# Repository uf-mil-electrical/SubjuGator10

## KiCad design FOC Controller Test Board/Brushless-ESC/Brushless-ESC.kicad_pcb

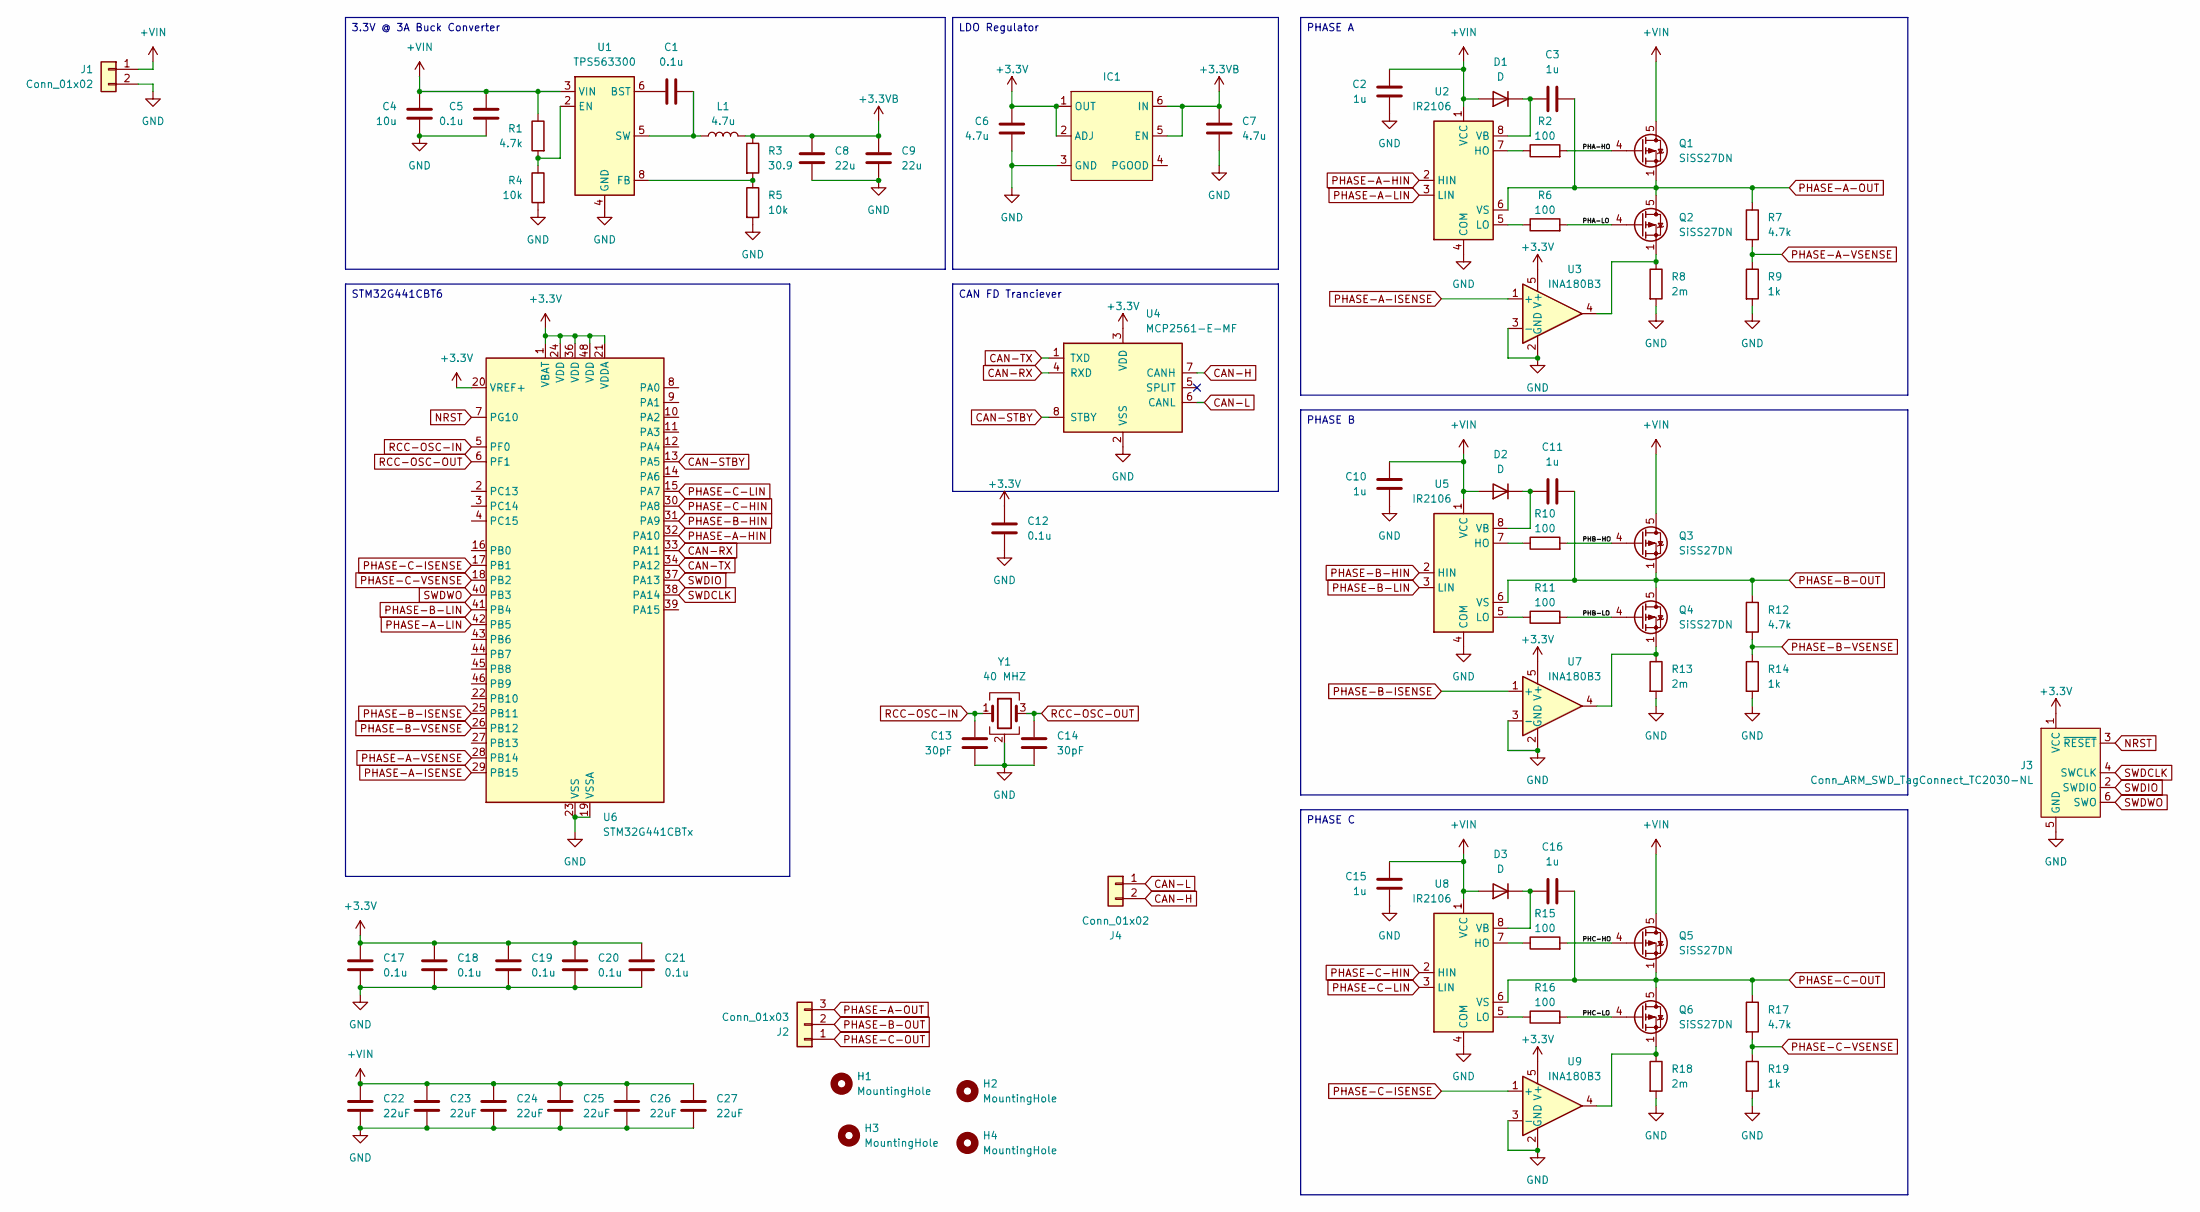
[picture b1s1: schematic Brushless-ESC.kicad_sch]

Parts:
C1, C5, C12, C17, C18, C19, C20, C21: 0.1u; C_0402_1005Metric
C2, C3, C10, C11, C15, C16: 1u; C_0603_1608Metric
C4: 10u; C_0805_2012Metric
C6, C7: 4.7u; C_0603_1608Metric
C8, C9: 22u; C_0805_2012Metric
C13, C14: 30pF; C_0402_1005Metric
C22, C23, C24, C25, C26, C27: 22uF; C_0805_2012Metric
D1, D2, D3: D; D_SOD-323
H1, H2, H3, H4: MountingHole; MountingHole_3.2mm_M3_Pad_Via
IC1: SON95P300X300X100-7N-D
J1: Conn_01x02; Wago_734-162_1x02_P3.50mm_Horizontal
J2: Conn_01x03; Wago_734-163_1x03_P3.50mm_Horizontal
J3: Conn_ARM_SWD_TagConnect_TC2030-NL; Tag-Connect_TC2030-IDC-NL_2x03_P1.27mm_Vertical
J4: Conn_01x02; TerminalBlock_Xinya_XY308-2.54-2P_1x02_P2.54mm_Horizontal
L1: 4.7u; L_Coilcraft_LPS3314
Q1, Q2, Q3, Q4, Q5, Q6: SiSS27DN; Vishay_PowerPAK_1212-8_Single
R1, R7, R12, R17: 4.7k; R_0402_1005Metric
R2, R6, R10, R11, R15, R16: 100; R_0402_1005Metric
R3: 30.9; R_0402_1005Metric
R4, R5: 10k; R_0402_1005Metric
R8, R13, R18: 2m; R_1206_3216Metric
R9, R14, R19: 1k; R_0402_1005Metric
U1: TPS563300; SOT-583-8
U2, U5, U8: IR2106; SOIC-8_3.9x4.9mm_P1.27mm
U3, U7, U9: INA180B3; SOT-23-5
U4: MCP2561-E-MF; DFN-8-1EP_3x3mm_P0.65mm_EP1.55x2.4mm
U6: STM32G441CBTx; LQFP-48_7x7mm_P0.5mm
Y1: 40 MHZ; Crystal_SMD_3225-4Pin_3.2x2.5mm

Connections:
+3.3V: C6.1, C12.1, C17.1, C18.1, C19.1, C20.1, C21.1, IC1.1 (OUT), IC1.2 (ADJ), J3.1 (VCC), U3.5 (V+), U4.3 (VDD), U6.1 (VBAT), U6.20 (VREF+), U6.21 (VDDA), U6.24 (VDD), U6.36 (VDD), U6.48 (VDD), U7.5 (V+), U9.5 (V+)
+3.3VB: C7.1, C8.1, C9.1, IC1.5 (EN), IC1.6 (IN), L1.2, R3.1
+VIN: C2.1, C4.1, C5.1, C10.1, C15.1, C22.1, C23.1, C24.1, C25.1, C26.1, C27.1, D1.2 (A), D2.2 (A), D3.2 (A), J1.1, Q1.5 (D), Q3.5 (D), Q5.5 (D), R1.1, U1.3 (VIN), U2.1 (VCC), U5.1 (VCC), U8.1 (VCC)
/PHA-HO: Q1.4 (G), R2.2
/PHA-LO: Q2.4 (G), R6.2
/PHB-HO: Q3.4 (G), R10.2
/PHB-LO: Q4.4 (G), R11.2
/PHC-HO: Q5.4 (G), R15.2
/PHC-LO: Q6.4 (G), R16.2
CAN-H: J4.2, U4.7 (CANH); also elsewhere on the board
CAN-L: J4.1, U4.6 (CANL); also elsewhere on the board
CAN-RX: U4.4 (RXD), U6.33 (PA11)
CAN-STBY: U4.8 (STBY), U6.13 (PA5)
CAN-TX: U4.1 (TXD), U6.34 (PA12)
GND: C2.2, C4.2, C5.2, C6.2, C7.2, C8.2, C9.2, C10.2, C12.2, C13.2, C14.2, C15.2, C17.2, C18.2, C19.2, C20.2, C21.2, C22.2, C23.2, C24.2, C25.2, C26.2, C27.2, IC1.3 (GND), IC1.7 (EPAD), J1.2, J3.5 (GND), R4.2, R5.2, R8.2, R9.2, R13.2, R14.2, R18.2, R19.2, U1.4 (GND), U2.4 (COM), U3.2 (GND), U3.3 (-), U4.2 (VSS), U4.9 (VSS), U5.4 (COM), U6.19 (VSSA), U6.23 (VSS), U6.35 (VSS), U6.47 (VSS), U7.2 (GND), U7.3 (-), U8.4 (COM), U9.2 (GND), U9.3 (-), Y1.2 (G), Y1.4 (G)
NRST: J3.3 (~RESET), U6.7 (PG10)
unnamed: C3.1, D1.1 (K), U2.8 (VB)
unnamed: C11.1, D2.1 (K), U5.8 (VB)
unnamed: C16.1, D3.1 (K), U8.8 (VB)
unnamed: Q2.1 (S), Q2.2 (S), Q2.3 (S), R8.1, U3.4
unnamed: Q4.1 (S), Q4.2 (S), Q4.3 (S), R13.1, U7.4
unnamed: Q6.1 (S), Q6.2 (S), Q6.3 (S), R18.1, U9.4
unnamed: C1.1, U1.6 (BST)
unnamed: R1.2, R4.1, U1.2 (EN)
unnamed: R3.2, R5.1, U1.8 (FB)
unnamed: C1.2, L1.1, U1.5 (SW)
unnamed: R2.1, U2.7 (HO)
unnamed: R6.1, U2.5 (LO)
unnamed: R10.1, U5.7 (HO)
unnamed: R11.1, U5.5 (LO)
unnamed: R15.1, U8.7 (HO)
unnamed: R16.1, U8.5 (LO)
PHASE-A-HIN: U2.2 (HIN), U6.32 (PA10)
PHASE-A-ISENSE: U3.1 (+), U6.29 (PB15)
PHASE-A-LIN: U2.3 (LIN), U6.42 (PB5)
PHASE-A-OUT: C3.2, J2.3, Q1.1 (S), Q1.2 (S), Q1.3 (S), Q2.5 (D), R7.1, U2.6 (VS)
PHASE-A-VSENSE: R7.2, R9.1, U6.28 (PB14)
PHASE-B-HIN: U5.2 (HIN), U6.31 (PA9)
PHASE-B-ISENSE: U6.25 (PB11), U7.1 (+)
PHASE-B-LIN: U5.3 (LIN), U6.41 (PB4)
PHASE-B-OUT: C11.2, J2.2, Q3.1 (S), Q3.2 (S), Q3.3 (S), Q4.5 (D), R12.1, U5.6 (VS)
PHASE-B-VSENSE: R12.2, R14.1, U6.26 (PB12)
PHASE-C-HIN: U6.30 (PA8), U8.2 (HIN)
PHASE-C-ISENSE: U6.17 (PB1), U9.1 (+)
PHASE-C-LIN: U6.15 (PA7), U8.3 (LIN)
PHASE-C-OUT: C16.2, J2.1, Q5.1 (S), Q5.2 (S), Q5.3 (S), Q6.5 (D), R17.1, U8.6 (VS)
PHASE-C-VSENSE: R17.2, R19.1, U6.18 (PB2)
RCC-OSC-IN: C13.1, U6.5 (PF0), Y1.1
RCC-OSC-OUT: C14.1, U6.6 (PF1), Y1.3
SWDCLK: J3.4 (SWCLK), U6.38 (PA14)
SWDIO: J3.2 (SWDIO), U6.37 (PA13)
SWDWO: J3.6 (SWO), U6.40 (PB3)

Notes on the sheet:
LDO Regulator
CAN FD Tranciever
STM32G441CBT6
PHASE B
PHASE C
3.3V @ 3A Buck Converter
PHASE A

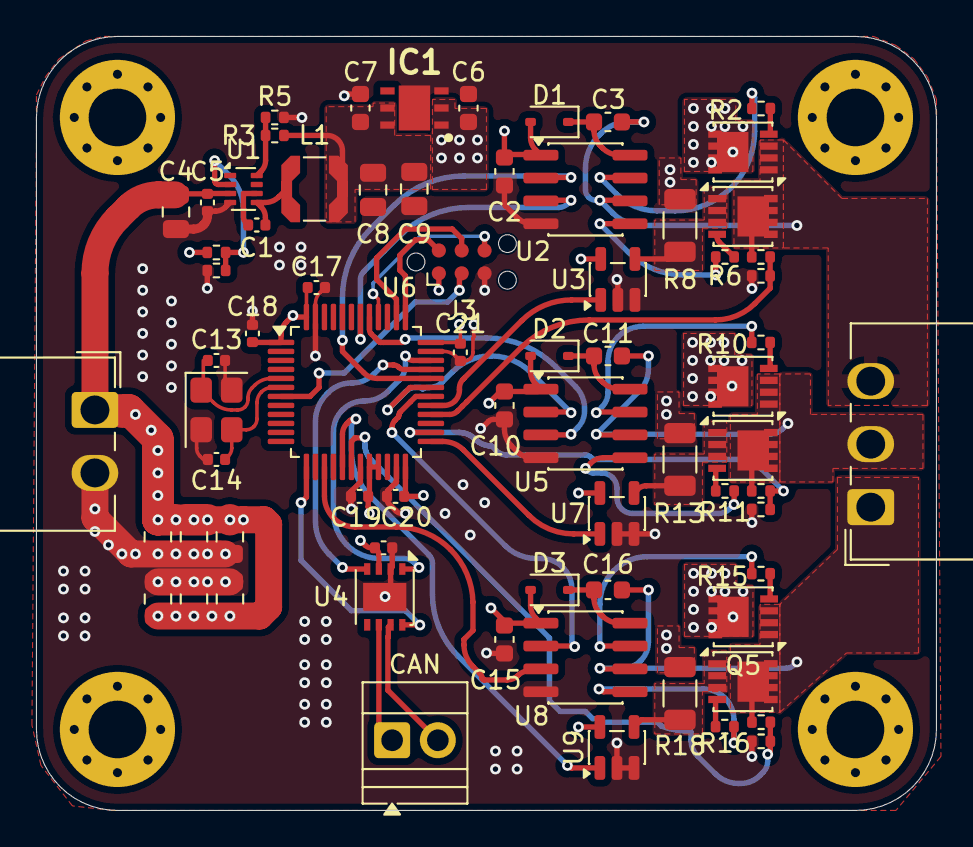
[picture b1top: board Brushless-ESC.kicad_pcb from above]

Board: 6 copper layers, 50.0 x 43.0 mm, 75 parts (0 on the bottom side), 52 nets.

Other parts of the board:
CAN: Conn_01x02; TerminalBlock_Xinya_XY308-2.54-2P_1x02_P2.54mm_Horizontal

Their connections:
CAN-H: CAN.2; also elsewhere on the board
CAN-L: CAN.1; also elsewhere on the board

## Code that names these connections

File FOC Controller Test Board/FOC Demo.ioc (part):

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Mcu.Name=STM32G441CBTx
Mcu.Package=LQFP48
Mcu.UserName=STM32G441CBTx
PA10.GPIOParameters=GPIO_Label
PA10.GPIO_Label=PHA-HIN
PA10.Signal=S_TIM1_CH3
PA11.Mode=FDCAN_Activate
PA11.Signal=FDCAN1_RX
PA12.Mode=FDCAN_Activate
PA12.Signal=FDCAN1_TX
PA13.Mode=Serial_Wire
PA13.Signal=SYS_JTMS-SWDIO
PA14.Mode=Serial_Wire
PA14.Signal=SYS_JTCK-SWCLK
PA7.GPIOParameters=GPIO_Label
PA7.GPIO_Label=PHC-LIN
PA7.Mode=Output Compare1 CH1N
PA7.Signal=TIM8_CH1N
PA8.GPIOParameters=GPIO_Label
PA8.GPIO_Label=PHC-HIN
PA8.Signal=S_TIM1_CH1
PA9.GPIOParameters=GPIO_Label
PA9.GPIO_Label=PHB-HIN
PA9.Signal=S_TIM1_CH2
PB1.Mode=IN12-Single-Ended
PB1.Signal=ADC1_IN12
PB11.Mode=IN14-Single-Ended
PB11.Signal=ADC1_IN14
PB12.Mode=IN11-Single-Ended
PB12.Signal=ADC1_IN11
PB14.Mode=IN5-Single-Ended
PB14.Signal=ADC1_IN5
PB15.Mode=IN15-Single-Ended
PB15.Signal=ADC2_IN15
PB2.Mode=IN12-Single-Ended
PB2.Signal=ADC2_IN12
PB4.GPIOParameters=GPIO_Label
PB4.GPIO_Label=PHB-LIN
PB4.Mode=Output Compare2 CH2N
PB4.Signal=TIM8_CH2N
PB5.GPIOParameters=GPIO_Label
PB5.GPIO_Label=PHA-LIN
PB5.Mode=PWM Generation3 CH3N
PB5.Signal=TIM8_CH3N
PF0-OSC_IN.Mode=HSE-External-Oscillator
PF0-OSC_IN.Signal=RCC_OSC_IN
PF1-OSC_OUT.Mode=HSE-External-Oscillator
PF1-OSC_OUT.Signal=RCC_OSC_OUT
RCC.HSE_VALUE=8000000
RCC.SYSCLKFreq_VALUE=16000000
board=custom
